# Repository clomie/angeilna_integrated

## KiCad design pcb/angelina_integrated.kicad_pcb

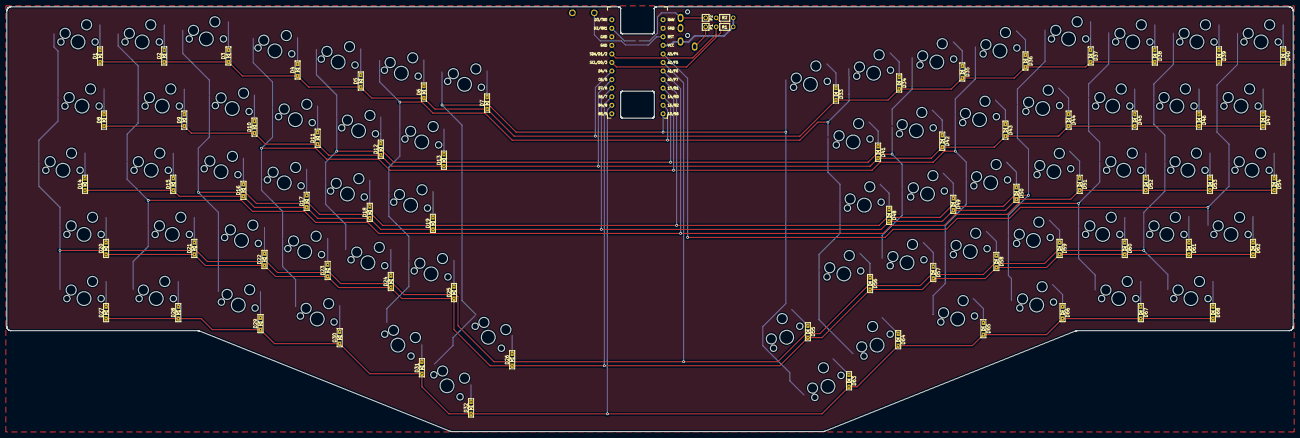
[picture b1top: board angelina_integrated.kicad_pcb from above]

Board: 2 copper layers, 381.9 x 126.1 mm, 144 parts (1 on the bottom side), 89 nets.

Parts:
D1, D2, D3, D4, D5, D6, D7, D8, D9, D10, D11, D12, D13, D14, D15, D16, D17, D18, D19, D20, D21, D22, D23, D24, D25, D26, D27, D28, D29, D30, D31, D32, D33, D34, D35, D36, D37, D38, D39, D40, D41, D42, D43, D44, D45, D46, D47, D48, D49, D50, D51, D52, D53, D54, D55, D56, D57, D58, D59, D60, D61, D62, D63, D64, D65, D66, D67, D68: D; D3_SMD
J1: MJ-4PP-9; MJ-4PP-9_1side
JP1: DATA-jumper; Jumper
P1: i2c-pin-A; 1pin_conn
P2: i2c-pin-B; 1pin_conn
R1, R2: R
RSW1: RESET; ResetSW
SW1, SW2, SW3, SW4, SW5, SW6, SW7, SW9, SW10, SW11, SW12, SW13, SW15, SW16, SW17, SW18, SW19, SW21, SW22, SW23, SW24, SW25, SW26, SW28, SW31, SW32, SW33, SW34, SW35, SW36, SW37, SW38, SW39, SW40, SW41, SW42, SW43, SW44, SW45, SW46, SW47, SW48, SW49, SW50, SW51, SW52, SW53, SW54, SW55, SW56, SW57, SW58, SW59, SW60, SW61, SW62, SW63, SW64, SW67: SW_PUSH; CherryMX_Hotswap_1u
SW8: SW_PUSH; CherryMX_Hotswap_1.5u
SW14, SW20: SW_PUSH; CherryMX_Hotswap_1.75u
SW27, SW29, SW30, SW65, SW66, SW68: SW_PUSH; CherryMX_Hotswap_1.25u
U1: ProMicro_r; ProMicro

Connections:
GND: J1.C, RSW1.2, U1.3, U1.4, U1.23
unnamed: D1.2, SW1.2
unnamed: D2.2, SW2.2
unnamed: D3.2, SW3.2
unnamed: D4.2, SW4.2
unnamed: D5.2, SW5.2
unnamed: D6.2, SW6.2
unnamed: D7.2, SW7.2
unnamed: D8.2, SW8.2
unnamed: D9.2, SW9.2
unnamed: D10.2, SW10.2
unnamed: D11.2, SW11.2
unnamed: D12.2, SW12.2
unnamed: D13.2, SW13.2
unnamed: D14.2, SW14.2
unnamed: D15.2, SW15.2
unnamed: D16.2, SW16.2
unnamed: D17.2, SW17.2
unnamed: D18.2, SW18.2
unnamed: D19.2, SW19.2
unnamed: D20.2, SW20.2
unnamed: D21.2, SW21.2
unnamed: D22.2, SW22.2
unnamed: D23.2, SW23.2
unnamed: D24.2, SW24.2
unnamed: D25.2, SW25.2
unnamed: D26.2, SW26.2
unnamed: D27.2, SW27.2
unnamed: D28.2, SW28.2
unnamed: D29.2, SW29.2
unnamed: D30.2, SW30.2
unnamed: D31.2, SW31.2
unnamed: D32.2, SW32.2
unnamed: D33.1, SW33.2
unnamed: D34.1, SW34.2
unnamed: D35.1, SW35.2
unnamed: D36.1, SW36.2
unnamed: D37.1, SW37.2
unnamed: D38.1, SW38.2
unnamed: D39.1, SW39.2
unnamed: D40.1, SW40.2
unnamed: D41.1, SW41.2
unnamed: D42.1, SW42.2
unnamed: D43.1, SW43.2
unnamed: D44.1, SW44.2
unnamed: D45.1, SW45.2
unnamed: D46.1, SW46.2
unnamed: D47.1, SW47.2
unnamed: D48.1, SW48.2
unnamed: D49.1, SW49.2
unnamed: D50.1, SW50.2
unnamed: D51.1, SW51.2
unnamed: D52.1, SW52.2
unnamed: D53.1, SW53.2
unnamed: D54.1, SW54.2
unnamed: D55.1, SW55.2
unnamed: D56.1, SW56.2
unnamed: D57.1, SW57.2
unnamed: D58.1, SW58.2
unnamed: D59.1, SW59.2
unnamed: D60.1, SW60.2
unnamed: D61.1, SW61.2
unnamed: D62.1, SW62.2
unnamed: D63.1, SW63.2
unnamed: D64.1, SW64.2
unnamed: D65.1, SW65.2
unnamed: D66.1, SW66.2
unnamed: D67.1, SW67.2
unnamed: D68.1, SW68.2
unnamed: J1.A, P1.1
unnamed: J1.B, JP1.1, P2.1
SCL: R2.1, U1.6
SDA: R1.1, U1.5
VCC: J1.D, R1.2, R2.2, U1.21
col0: SW40.1, SW47.1, SW54.1, SW62.1, U1.20
col1: SW1.1, SW8.1, SW14.1, SW20.1, SW27.1, SW39.1, SW46.1, SW53.1, SW61.1, SW68.1, U1.19
col2: SW2.1, SW9.1, SW15.1, SW21.1, SW28.1, SW38.1, SW45.1, SW52.1, SW60.1, SW67.1, U1.18
col3: SW3.1, SW10.1, SW16.1, SW22.1, SW29.1, SW37.1, SW44.1, SW51.1, SW59.1, SW66.1, U1.17
col4: SW4.1, SW11.1, SW17.1, SW23.1, SW30.1, SW36.1, SW43.1, SW50.1, SW58.1, SW65.1, U1.16
col5: SW5.1, SW12.1, SW18.1, SW24.1, SW35.1, SW42.1, SW49.1, SW57.1, U1.15
col6: SW6.1, SW13.1, SW19.1, SW25.1, SW31.1, SW34.1, SW41.1, SW48.1, SW56.1, SW64.1, U1.14
col7: SW7.1, SW26.1, SW32.1, SW33.1, SW55.1, SW63.1, U1.13
data: JP1.2, U1.2
reset: RSW1.1, U1.22
row0: D1.1, D2.1, D3.1, D4.1, D5.1, D6.1, D7.1, D33.2, D34.2, D35.2, D36.2, D37.2, D38.2, D39.2, D40.2, U1.7
row1: D8.1, D9.1, D10.1, D11.1, D12.1, D13.1, D41.2, D42.2, D43.2, D44.2, D45.2, D46.2, D47.2, U1.8
row2: D14.1, D15.1, D16.1, D17.1, D18.1, D19.1, D48.2, D49.2, D50.2, D51.2, D52.2, D53.2, D54.2, U1.9
row3: D20.1, D21.1, D22.1, D23.1, D24.1, D25.1, D26.1, D55.2, D56.2, D57.2, D58.2, D59.2, D60.2, D61.2, D62.2, U1.10
row4: D27.1, D28.1, D29.1, D30.1, D31.1, D32.1, D63.2, D64.2, D65.2, D66.2, D67.2, D68.2, U1.11

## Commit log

2020-03-07 Add layout files
2020-03-12 update layout
2020-03-21 update layout file
2020-03-29 Added schematic and footprints
2020-04-04 Finished to draw circuit
2020-04-04 Fix pcb
2020-04-04 Add cross position scad
2020-04-23 Finished to make pcb
2020-06-20 Update scad
2020-06-20 Add credit
2020-06-20 Rename layout files
2020-06-20 Add ordered files
2020-07-11 Update case design
2020-07-11 Add case data
2021-01-31 Add foam design
2021-01-31 Add ordered foam data
